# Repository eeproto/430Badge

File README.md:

# ECET 430 Solder Practice Board: Badge

This is a KiCad design to practice surface mount soldering.

## Purpose

Easy surface mount and a few through hole parts to practice working with a stencil, pick and place, and reflow soldering.

## Repo Layout

- `kicad` KiCad project with schematic, pcb layout
- `graphics` Graphic files for outline and silk development
- `fabrication` BOM and Gerbers for manufacturing
- `plots` Board renderings and schematic

## Usage

Practice board assembly by hand or with tools available.

## Design

The CMOS version of the popular 555 timer drives 8 LEDs. Configured as an astable multivibrator, its timing is determined by an RC combination.Four LEDs are active on the low portion of the output square wave, and four are set to be active on high or low based on solder jumper settings.

## Author

Written by Christian H, info@eeproto.com, 2024

## License

This work is available under the [Creative Commons Attribution-ShareAlike License 4.0](https://creativecommons.org/licenses/by-nc-sa/4.0/) CC BY-NC-SA 4.0.

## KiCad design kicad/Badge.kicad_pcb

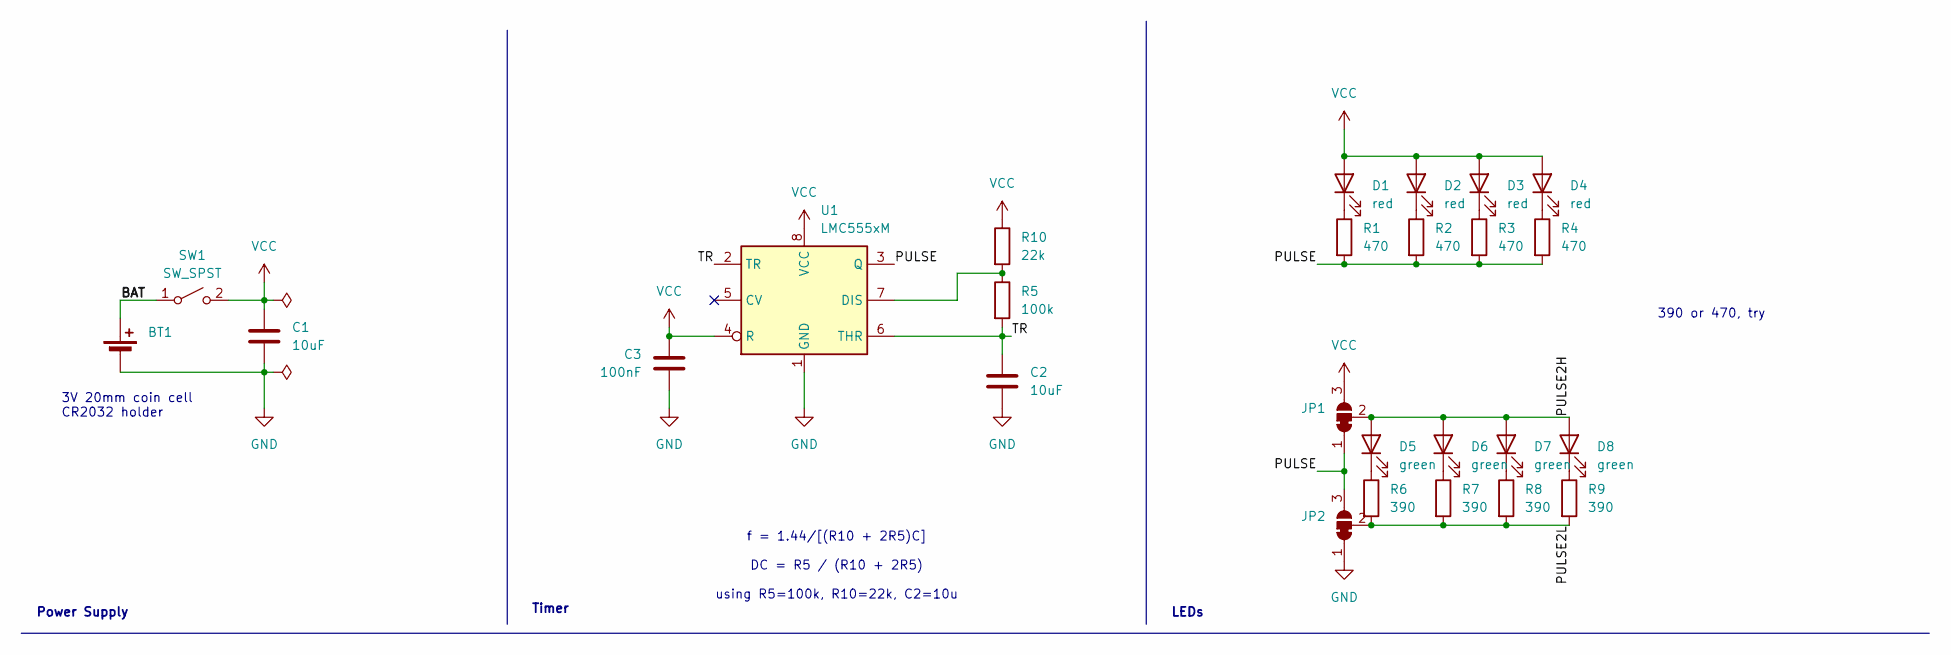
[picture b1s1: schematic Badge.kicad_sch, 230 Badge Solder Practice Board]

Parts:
BT1: Battery_Cell; BatteryHolder_Keystone_103_1x20mm; MPN 36-103-ND
C1, C2: 10uF; C_0805_2012Metric_Pad1.18x1.45mm_HandSolder; MPN CAP CER 10UF 16V 0805
C3: 100nF; C_0805_2012Metric_Pad1.18x1.45mm_HandSolder; MPN CAP CER 0.1UF 25V 0805
D1, D2, D3, D4: red; LED_0805_2012Metric_Pad1.15x1.40mm_HandSolder; MPN QBLP631-R5-2897
D5, D6, D7, D8: green; LED_0805_2012Metric_Pad1.15x1.40mm_HandSolder; MPN QBLP631-AG1
JP1, JP2: SolderJumper_3_Bridged12; SolderJumper-3_P1.3mm_Bridged12_RoundedPad1.0x1.5mm
R1, R2, R3, R4: 470; R_0805_2012Metric_Pad1.20x1.40mm_HandSolder; MPN RES 470 OHM 1/8W 0805
R5: 100k; R_0805_2012Metric_Pad1.20x1.40mm_HandSolder; MPN RES 100K OHM 1/8W 0805
R6, R7, R8, R9: 390; R_0805_2012Metric_Pad1.20x1.40mm_HandSolder; MPN RES 390 OHM 1/8W 0805
R10: 22k; R_0805_2012Metric_Pad1.20x1.40mm_HandSolder; MPN RES 22K OHM 1/8W 0805
SW1: SW_SPST; SW_DIP_SPSTx01_Slide_9.78x4.72mm_W7.62mm_P2.54mm; MPN DS01-254-L-01BE
U1: LMC555xM; SOIC-8_3.9x4.9mm_P1.27mm; MPN LMC555CMX/NOPB

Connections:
/BAT: BT1.1 (+), SW1.1 (A)
/PULSE: JP1.1 (A), JP2.3 (B), R1.2, R2.2, R3.2, R4.2, U1.3 (Q)
/PULSE2H: D5.2 (A), D6.2 (A), D7.2 (A), D8.2 (A), JP1.2 (C)
/PULSE2L: JP2.2 (C), R6.2, R7.2, R8.2, R9.2
/TR: C2.1, R5.2, U1.2 (TR), U1.6 (THR)
GND: BT1.2 (-), C1.2, C2.2, C3.2, JP2.1 (A), U1.1 (GND)
unnamed: D1.1 (K), R1.1
unnamed: D2.1 (K), R2.1
unnamed: D3.1 (K), R3.1
unnamed: D4.1 (K), R4.1
unnamed: D5.1 (K), R6.1
unnamed: D6.1 (K), R7.1
unnamed: D7.1 (K), R8.1
unnamed: D8.1 (K), R9.1
unnamed: R5.1, R10.2, U1.7 (DIS)
VCC: C1.1, C3.1, D1.2 (A), D2.2 (A), D3.2 (A), D4.2 (A), JP1.3 (B), R10.1, SW1.2 (B), U1.4 (R), U1.8 (VCC)

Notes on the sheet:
390 or 470, try
LEDs
Power Supply
Timer
f = 1.44/[(R10 + 2R5)C] DC = R5 / (R10 + 2R5) using R5=100k, R10=22k, C2=10u
3V 20mm coin cell CR2032 holder

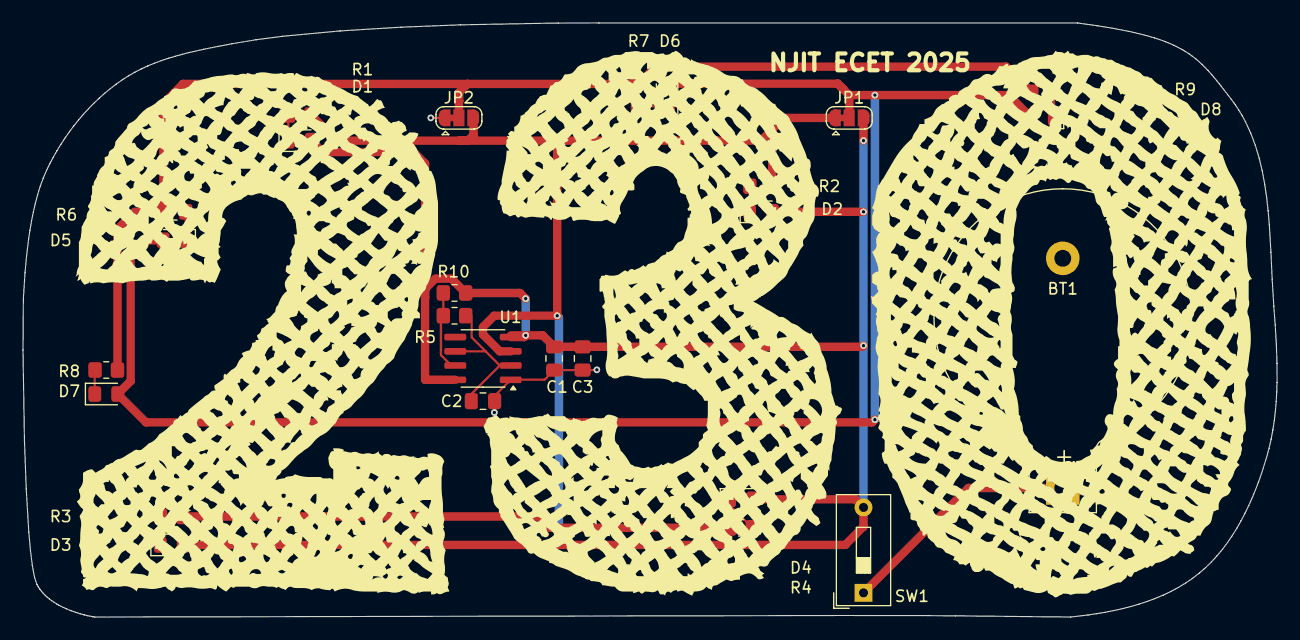
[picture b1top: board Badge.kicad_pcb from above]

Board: 2 copper layers, 111.9 x 53.0 mm, 26 parts (0 on the bottom side), 16 nets.

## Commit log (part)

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2024-10-02 outline draft 3
2024-10-02 routing 1
2024-10-22 fix routing, straight edge sections for solderpaste, milling gerbers
2024-10-27 router print one
2024-11-11 fix discrepancies with milled board, to be milled again
2024-11-13 fab files 1
2024-11-13 fabrication fix missing bottom mask
2024-12-01 ibom
2024-12-01 fabrication fix
2025-10-29 230 refactor

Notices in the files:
kicad/Badge.kicad_pcb:
Open Source Hardware CC BY-NC-SA 4.0
